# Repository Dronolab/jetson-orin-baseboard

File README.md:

# Dronolab Jetson Orin Carrier Board

Modified Version of [Jetson Orin Baseboard](https://github.com/antmicro/jetson-orin-baseboard) by [Antmicro](https://www.antmicro.com)

## Overview

This project contains hardware design files for a carrier board supporting NVIDIA Jetson Orin Nano and Jetson Orin NX System on Modules (SoMs). The board break-routes the typical IO interfaces from the SoM. Additionally, it exposes an expansion connector also known as the Payload Area Connector (PAC) that allows for an electrical connection for monitoring and control of any payload.

The design files were preapared in KiCad 7.x.

## Quick Start

Install Kicad's Latest Stable Release and Github Desktop. Clone this project using Github Desktop and make sure to set the option to contributing to the Dronolab Repository (not the Antmicro one). To make a change, create your own branch that describes the change being made. Once you are done, commit and push your changes. Finally, merge your branch to main and wait for approval.

## Key features

* DC Power connector
* MIPI CSI-2 interfaces
* USB-C 10 Gbps with DP Alternate Mode
* USB-C 10 Gbps + USB-C Uart
* M.2 key M for SSD
* 1Gb Ethernet
* Custom Payload Area Connector (PAC)
* RTC battery backup

## Project structure

The main directory contains KiCad PCB project files, a LICENSE, and a README.
The remaining files are stored in the following directories:

* `lib` - contains the component libraries
* `img` - contains graphics for this README
* `doc` - contains schematics in pdf form

## Licensing

This project is published under the [Apache-2.0](LICENSE) license.

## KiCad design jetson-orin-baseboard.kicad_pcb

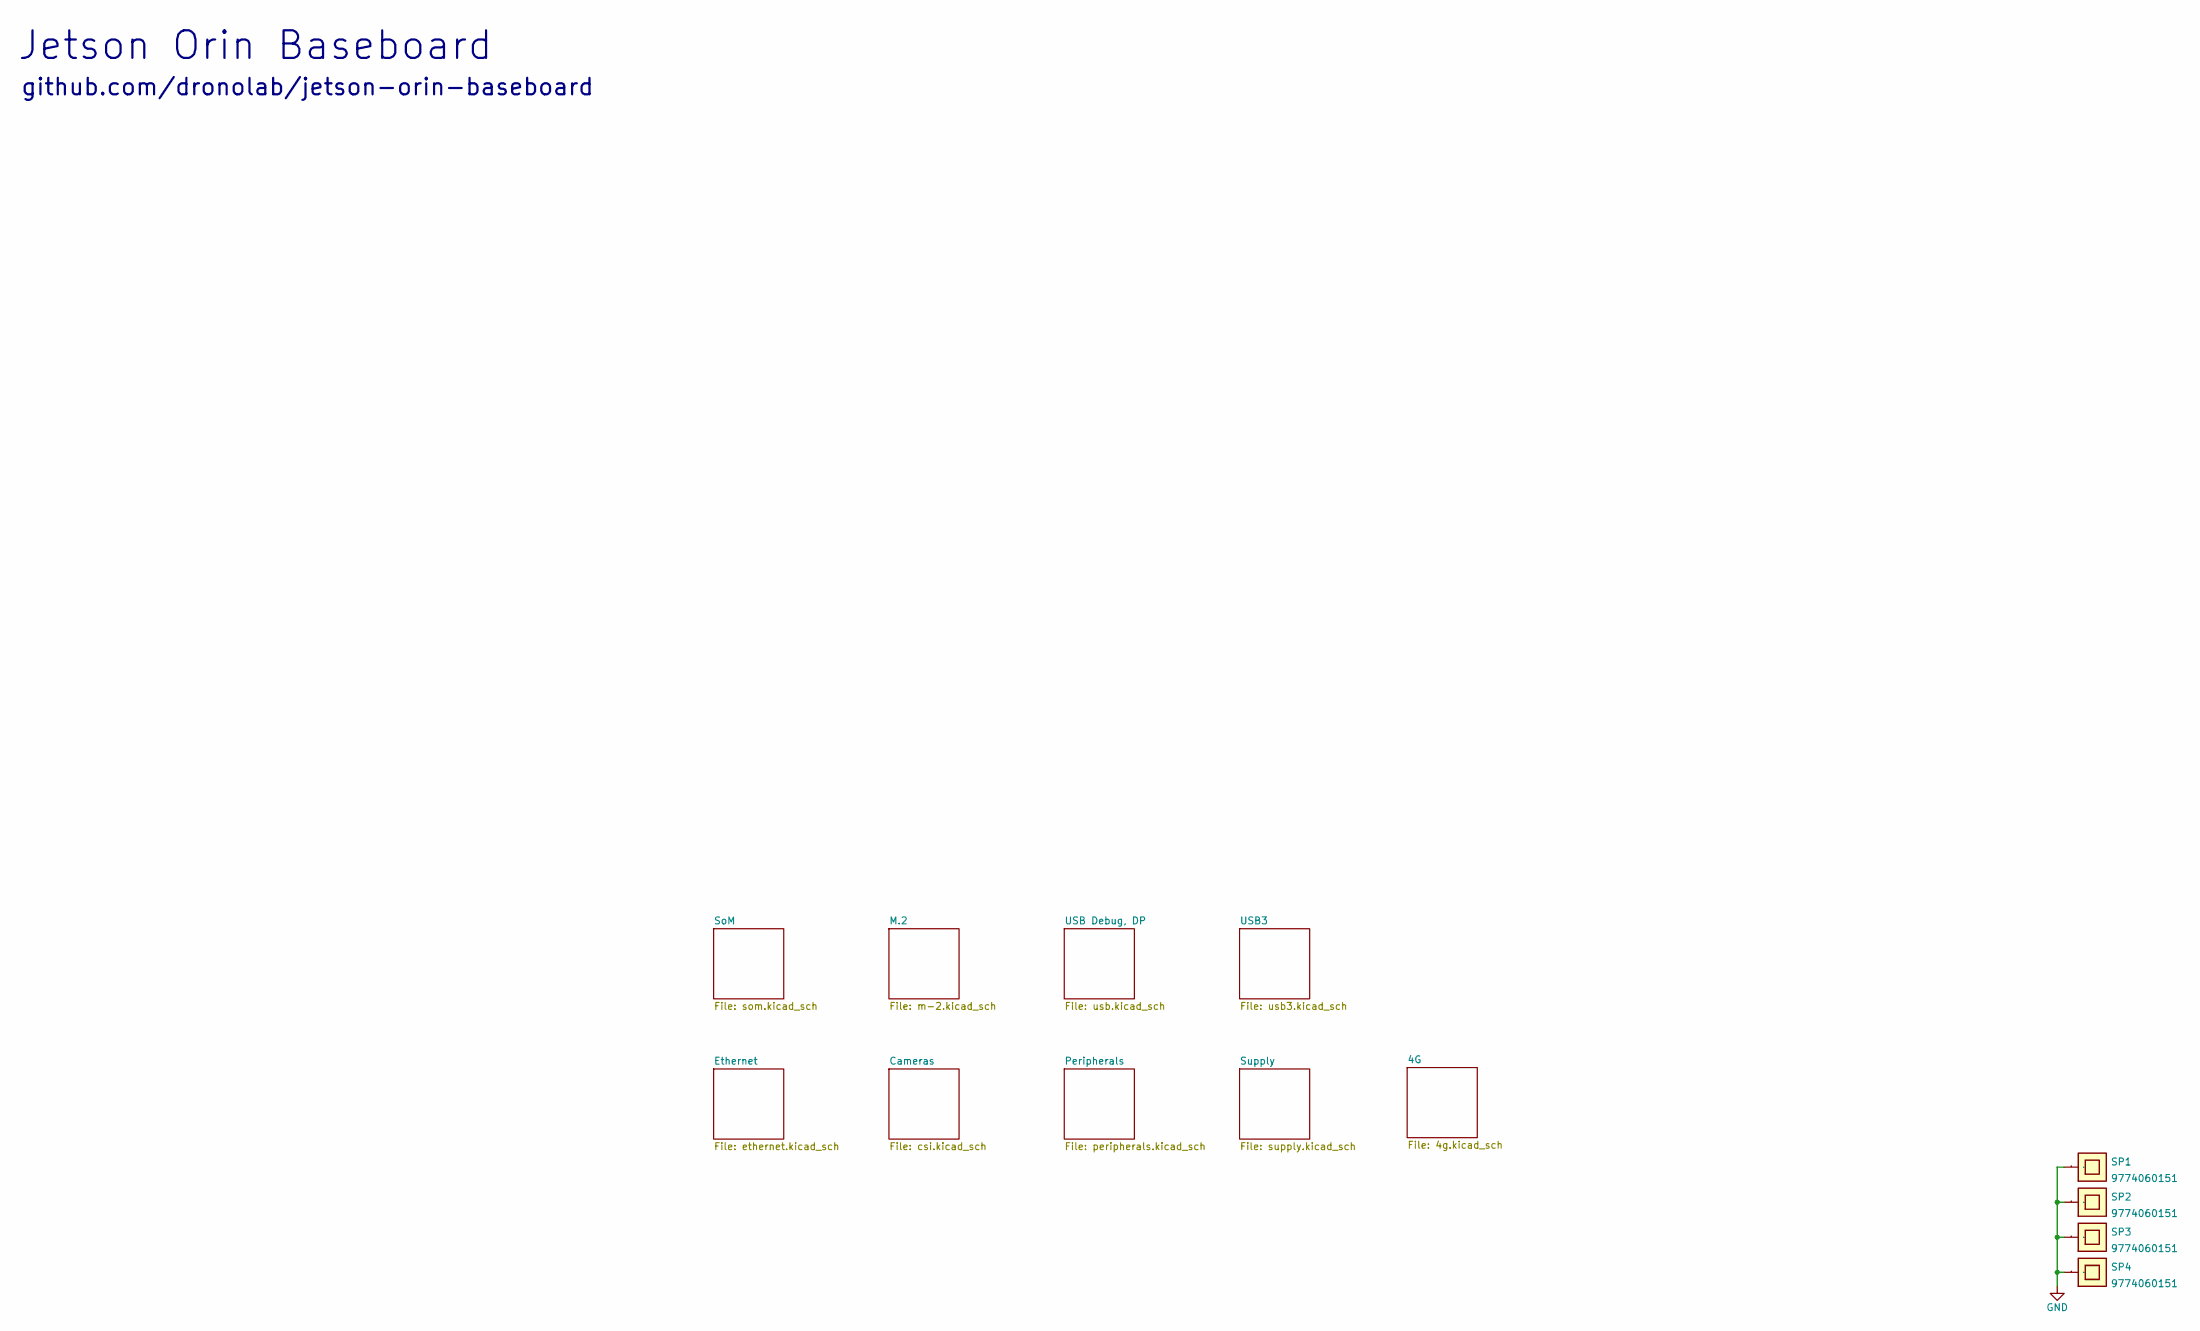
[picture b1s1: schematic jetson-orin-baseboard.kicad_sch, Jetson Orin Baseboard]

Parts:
SP1, SP2, SP3, SP4: 9774060151; MPN 9774060151

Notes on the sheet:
github.com/dronolab/jetson-orin-baseboard
Jetson Orin Baseboard

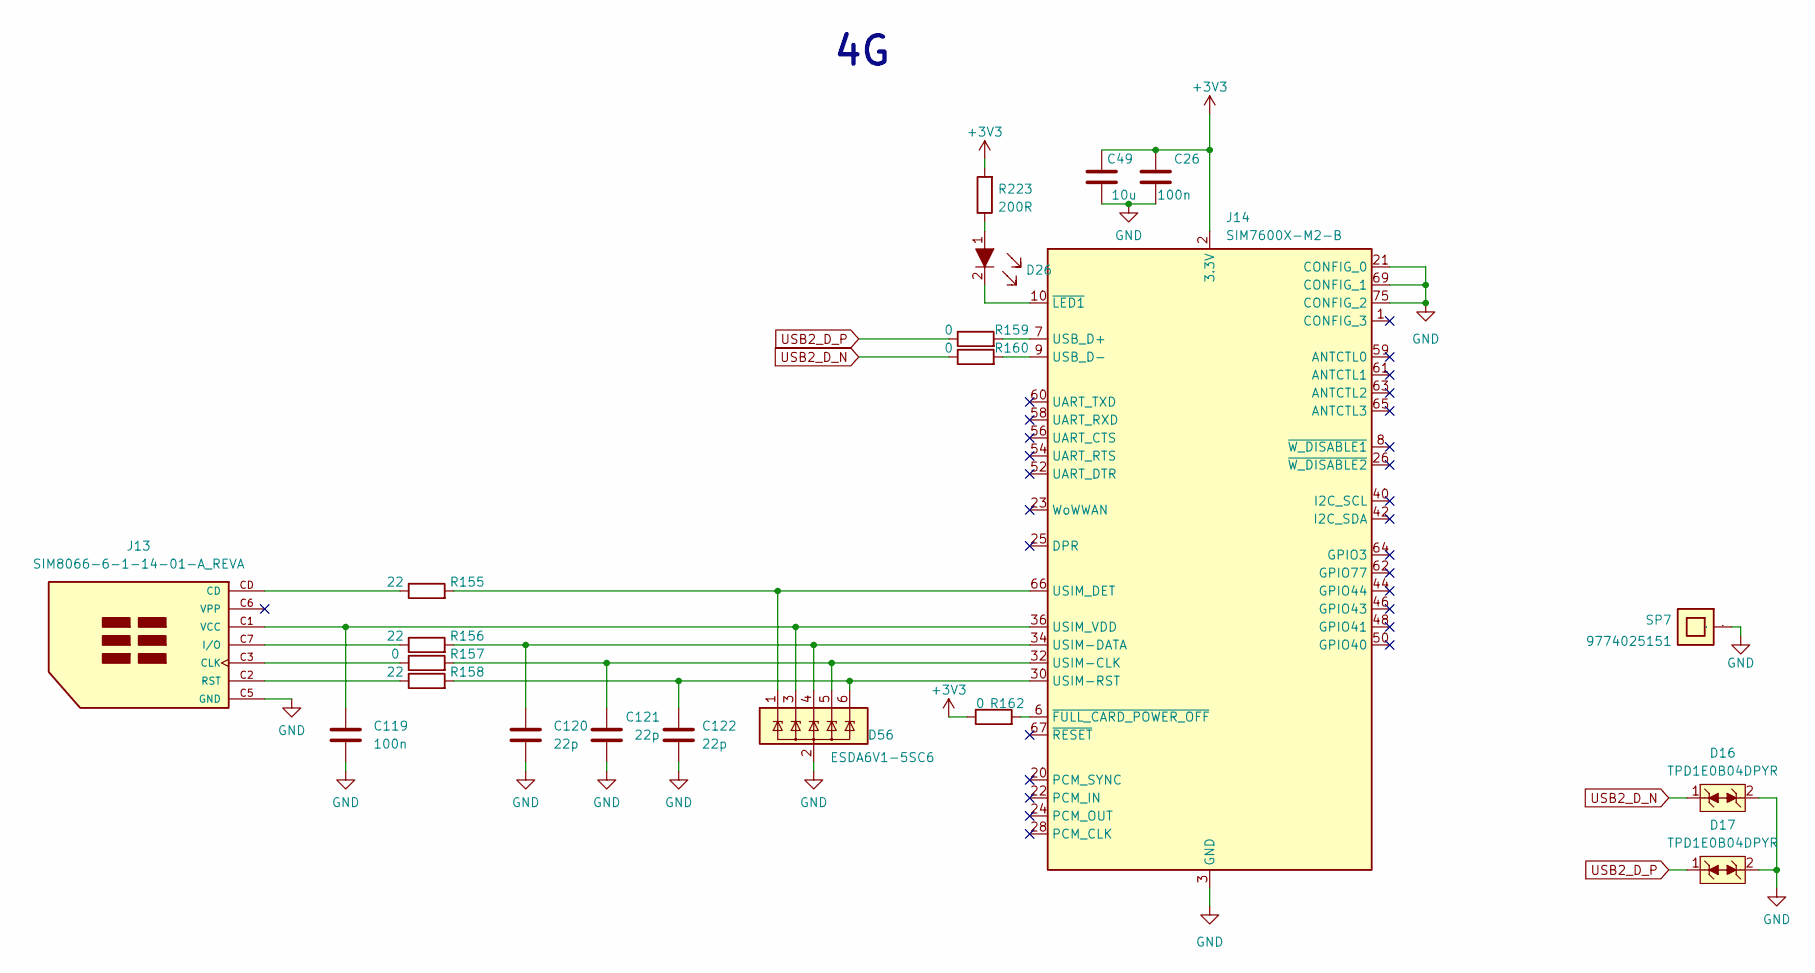
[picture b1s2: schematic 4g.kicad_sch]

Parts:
C26: C_100n_0402; 0402-cap; MPN GRM155R61H104KE14D
C49: C_10u_0402; 0402-cap; MPN CC0402MRX5R5BB106
C119: 100n; 0402-cap
C120, C121, C122: 22p; 0402-cap
D16, D17: TPD1E0B04DPYR; XDFN-2_1x0.60mm; MPN TPD1E0B04DPYR
D26: LTST-C190GKT; LED_0603; MPN LTST-C190GKT
D56: ESDA6V1-5SC6; SOT-23-6
J13: SIM8066-6-1-14-01-A_REVA; GCT_SIM8066-6-1-14-01-A_REVA; PARTREV REVA
J14: SIM7600X-M2-B; TE_2199230-3
R155, R156, R158: 22; 0402-res
R157, R159, R160, R162: 0; 0402-res
R223: R_200R_0402; 0402-res; MPN RC0402FR-07200RL
SP7: 9774025151; MPN 9774025151

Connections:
unnamed: D56.1 (IO1), J14.66 (USIM_DET), R155.2
unnamed: C119.1, D56.3 (IO2), J13.C1 (VCC), J14.36 (USIM_VDD)
unnamed: C120.1, D56.4 (IO3), J14.34 (USIM-DATA), R156.2
unnamed: C121.1, D56.5 (IO4), J14.32 (USIM-CLK), R157.2
unnamed: C122.1, D56.6 (IO5), J14.30 (USIM-RST), R158.2
unnamed: J13.C3 (CLK), R157.1
unnamed: J13.C7 (I/O), R156.1
unnamed: J13.CD, R155.1
unnamed: J13.C2 (RST), R158.1
unnamed: J14.7 (USB_D+), R159.2
unnamed: J14.9 (USB_D-), R160.2
unnamed: J14.6 (~FULL_CARD_POWER_OFF), R162.2
USB2_D_N: D16.1, R160.1; also elsewhere on the board
USB2_D_P: D17.1, R159.1; also elsewhere on the board

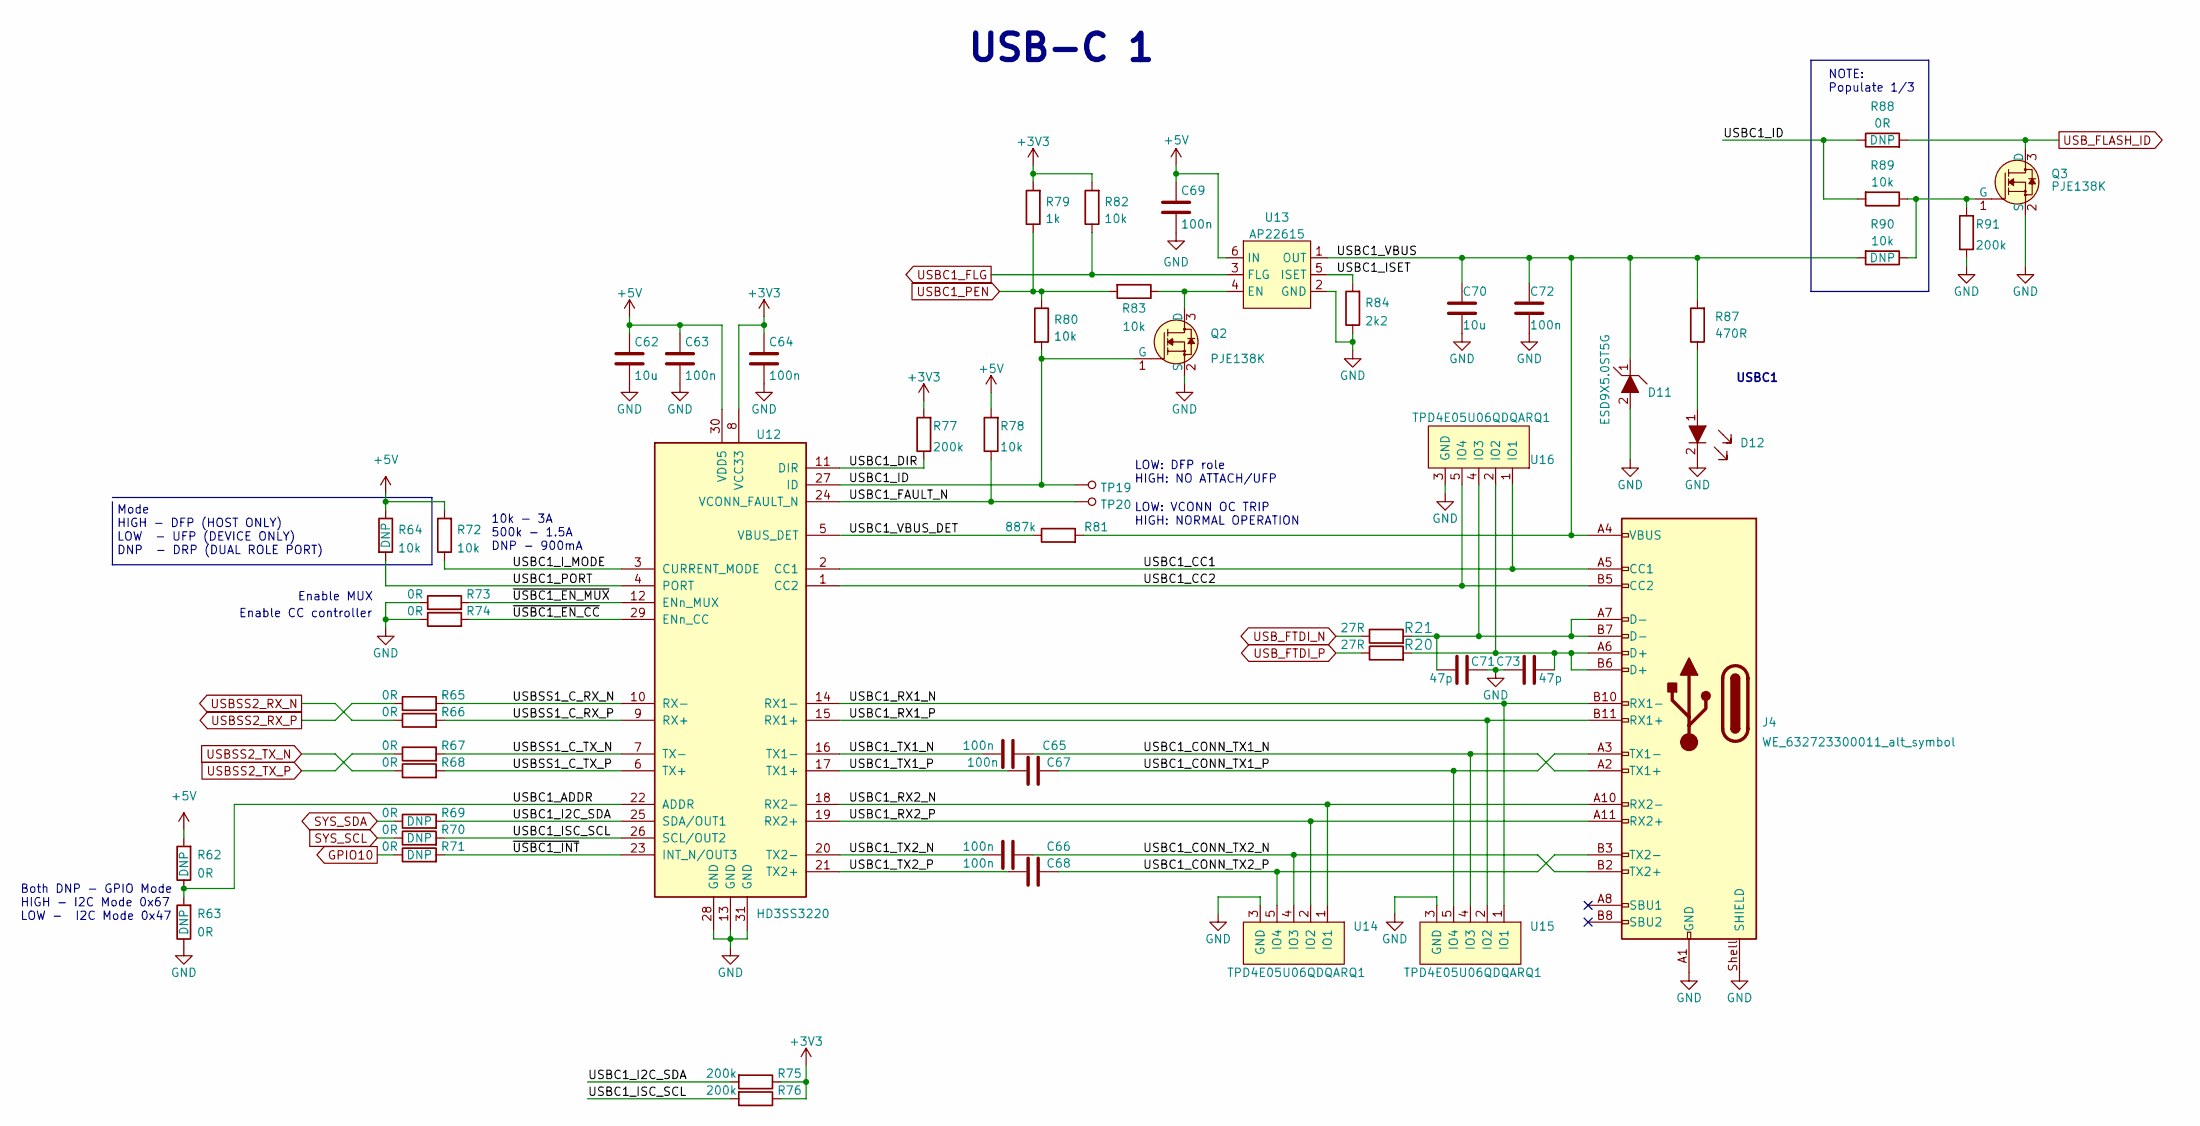
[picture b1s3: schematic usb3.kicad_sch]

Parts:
C62, C70: C_10u_0603; 0603-cap; MPN GRM188R61A106KE69D
C63, C64, C65, C66, C67, C68, C69, C72: C_100n_0402; 0402-cap; MPN GRM155R61H104KE14D
C71, C73: 47p; 0402-cap
D11: ESD9X5.0ST5G; SOD-923; MPN ESD9X5.0ST5G
D12: LTST-C190GKT; LED_0603; MPN LTST-C190GKT
J4: WE_632723300011_alt_symbol; WE_632723300011; MPN 632723300011
Q2, Q3: PJE138K; SOT-523; MPN PJE138K_R1_00001
R20, R21: R_27R_0402; 0402-res; MPN CRCW040227R0FKEDC
R62, R63, R65, R66, R67, R68, R69, R70, R71, R73, R74, R88: R_0R_0402; 0402-res; MPN ERJ2GE0R00X
R64, R72, R78, R80, R82, R83, R89, R90: R_10k_0402; 0402-res; MPN CRCW040210K0FKEDHP
R75, R76, R77, R91: R_200k_0402; 0402-res; MPN RC0402FR-07200KL
R79: R_1k_0402; 0402-res; MPN CR0402-FX-1001GLF
R81: R_887k_0402; 0402-res; MPN CR0402-FX-8873GLF
R84: R_2k2_0402; 0402-res; MPN RC0402FR-072K2L
R87: R_470R_0402; 0402-res; MPN CRCW0402470RFKED
TP19, TP20: TP_SMD_0_75MM; Testpoint_smd_0_75mm
U12: HD3SS3220; RNH0030A; MPN HD3SS3220RNHT
U13: AP22615; TSOT23-6; MPN AP22615AWU-7
U14, U15, U16: TPD4E05U06QDQARQ1; USON-10_2.5x1.0mm_P0.5mm; MPN TPD4E05U06QDQARQ1

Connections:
/USB3/USBC1_ADDR: R62.1, R63.2, U12.22 (ADDR)
/USB3/USBC1_CC1: J4.A5 (CC1), U12.2 (CC1), U16.1 (IO1), U16.10 (IO1)
/USB3/USBC1_CC2: J4.B5 (CC2), U12.1 (CC2), U16.5 (IO4), U16.6 (IO4)
/USB3/USBC1_CONN_TX1_N: C65.2, J4.A2 (TX1+), U15.4 (IO3), U15.7 (IO3)
/USB3/USBC1_CONN_TX1_P: C67.2, J4.A3 (TX1-), U15.5 (IO4), U15.6 (IO4)
/USB3/USBC1_CONN_TX2_N: C66.2, J4.B2 (TX2+), U14.4 (IO3), U14.7 (IO3)
/USB3/USBC1_CONN_TX2_P: C68.2, J4.B3 (TX2-), U14.5 (IO4), U14.6 (IO4)
/USB3/USBC1_DIR: R77.1, U12.11 (DIR)
/USB3/USBC1_FAULT_N: R78.1, TP20.1, U12.24 (VCONN_FAULT_N)
/USB3/USBC1_I2C_SDA: R69.2, R75.2, U12.25 (SDA/OUT1)
/USB3/USBC1_ID: Q2.1 (G), R80.2, R88.1, R89.2, TP19.1, U12.27 (ID)
/USB3/USBC1_ISC_SCL: R70.2, R76.2, U12.26 (SCL/OUT2)
/USB3/USBC1_ISET: R84.2, U13.5 (ISET)
/USB3/USBC1_I_MODE: R72.1, U12.3 (CURRENT_MODE)
/USB3/USBC1_PORT: R64.2, U12.4 (PORT)
/USB3/USBC1_RX1_N: J4.B10 (RX1-), U12.14 (RX1-), U15.1 (IO1), U15.10 (IO1)
/USB3/USBC1_RX1_P: J4.B11 (RX1+), U12.15 (RX1+), U15.2 (IO2), U15.9 (IO2)
/USB3/USBC1_RX2_N: J4.A10 (RX2-), U12.18 (RX2-), U14.1 (IO1), U14.10 (IO1)
/USB3/USBC1_RX2_P: J4.A11 (RX2+), U12.19 (RX2+), U14.2 (IO2), U14.9 (IO2)
/USB3/USBC1_TX1_N: C65.1, U12.16 (TX1-)
/USB3/USBC1_TX1_P: C67.1, U12.17 (TX1+)
/USB3/USBC1_TX2_N: C66.1, U12.20 (TX2-)
/USB3/USBC1_TX2_P: C68.1, U12.21 (TX2+)
/USB3/USBC1_VBUS: C70.1, C72.1, D11.1, J4.A4 (VBUS), J4.A9 (VBUS), J4.B4 (VBUS), J4.B9 (VBUS), R81.2, R87.2, R90.2, U13.1 (OUT)
/USB3/USBC1_VBUS_DET: R81.1, U12.5 (VBUS_DET)
/USB3/USBSS1_C_RX_N: R65.2, U12.10 (RX-)
/USB3/USBSS1_C_RX_P: R66.2, U12.9 (RX+)
/USB3/USBSS1_C_TX_N: R67.2, U12.7 (TX-)
/USB3/USBSS1_C_TX_P: R68.2, U12.6 (TX+)
/USB3/~USBC1_EN_CC: R74.2, U12.29 (ENn_CC)
/USB3/~USBC1_EN_MUX: R73.2, U12.12 (ENn_MUX)
/USB3/~USBC1_INT: R71.2, U12.23 (INT_N/OUT3)
/USB Debug, DP/PDC_CTL1: R21.1; also elsewhere on the board
GPIO10: R71.1; also elsewhere on the board
unnamed: D12.1, R87.1
unnamed: Q2.3 (D), R83.1, U13.4 (EN)
unnamed: Q3.1 (G), R89.1, R90.1, R91.2
SYS_SCL: R70.1; also elsewhere on the board
SYS_SDA: R69.1; also elsewhere on the board
USBC1_FLG: R82.1, U13.3 (FLG); also elsewhere on the board
USBC1_PEN: R79.1, R80.1, R83.2; also elsewhere on the board
USBSS2_RX_N: R66.1; also elsewhere on the board
USBSS2_RX_P: R65.1; also elsewhere on the board
USBSS2_TX_N: R68.1; also elsewhere on the board
USBSS2_TX_P: R67.1; also elsewhere on the board
USB_FLASH_ID: Q3.3 (D), R88.2; also elsewhere on the board

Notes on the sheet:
Mode HIGH - DFP (HOST ONLY) LOW - UFP (DEVICE ONLY) DNP - DRP (DUAL ROLE PORT)
Enable MUX
Both DNP - GPIO Mode HIGH - I2C Mode 0x67 LOW - I2C Mode 0x47
USB-C 1
10k - 3A 500k - 1.5A DNP - 900mA
LOW: DFP role HIGH: NO ATTACH/UFP
NOTE: Populate 1/3
USBC1
LOW: VCONN OC TRIP HIGH: NORMAL OPERATION
Enable CC controller

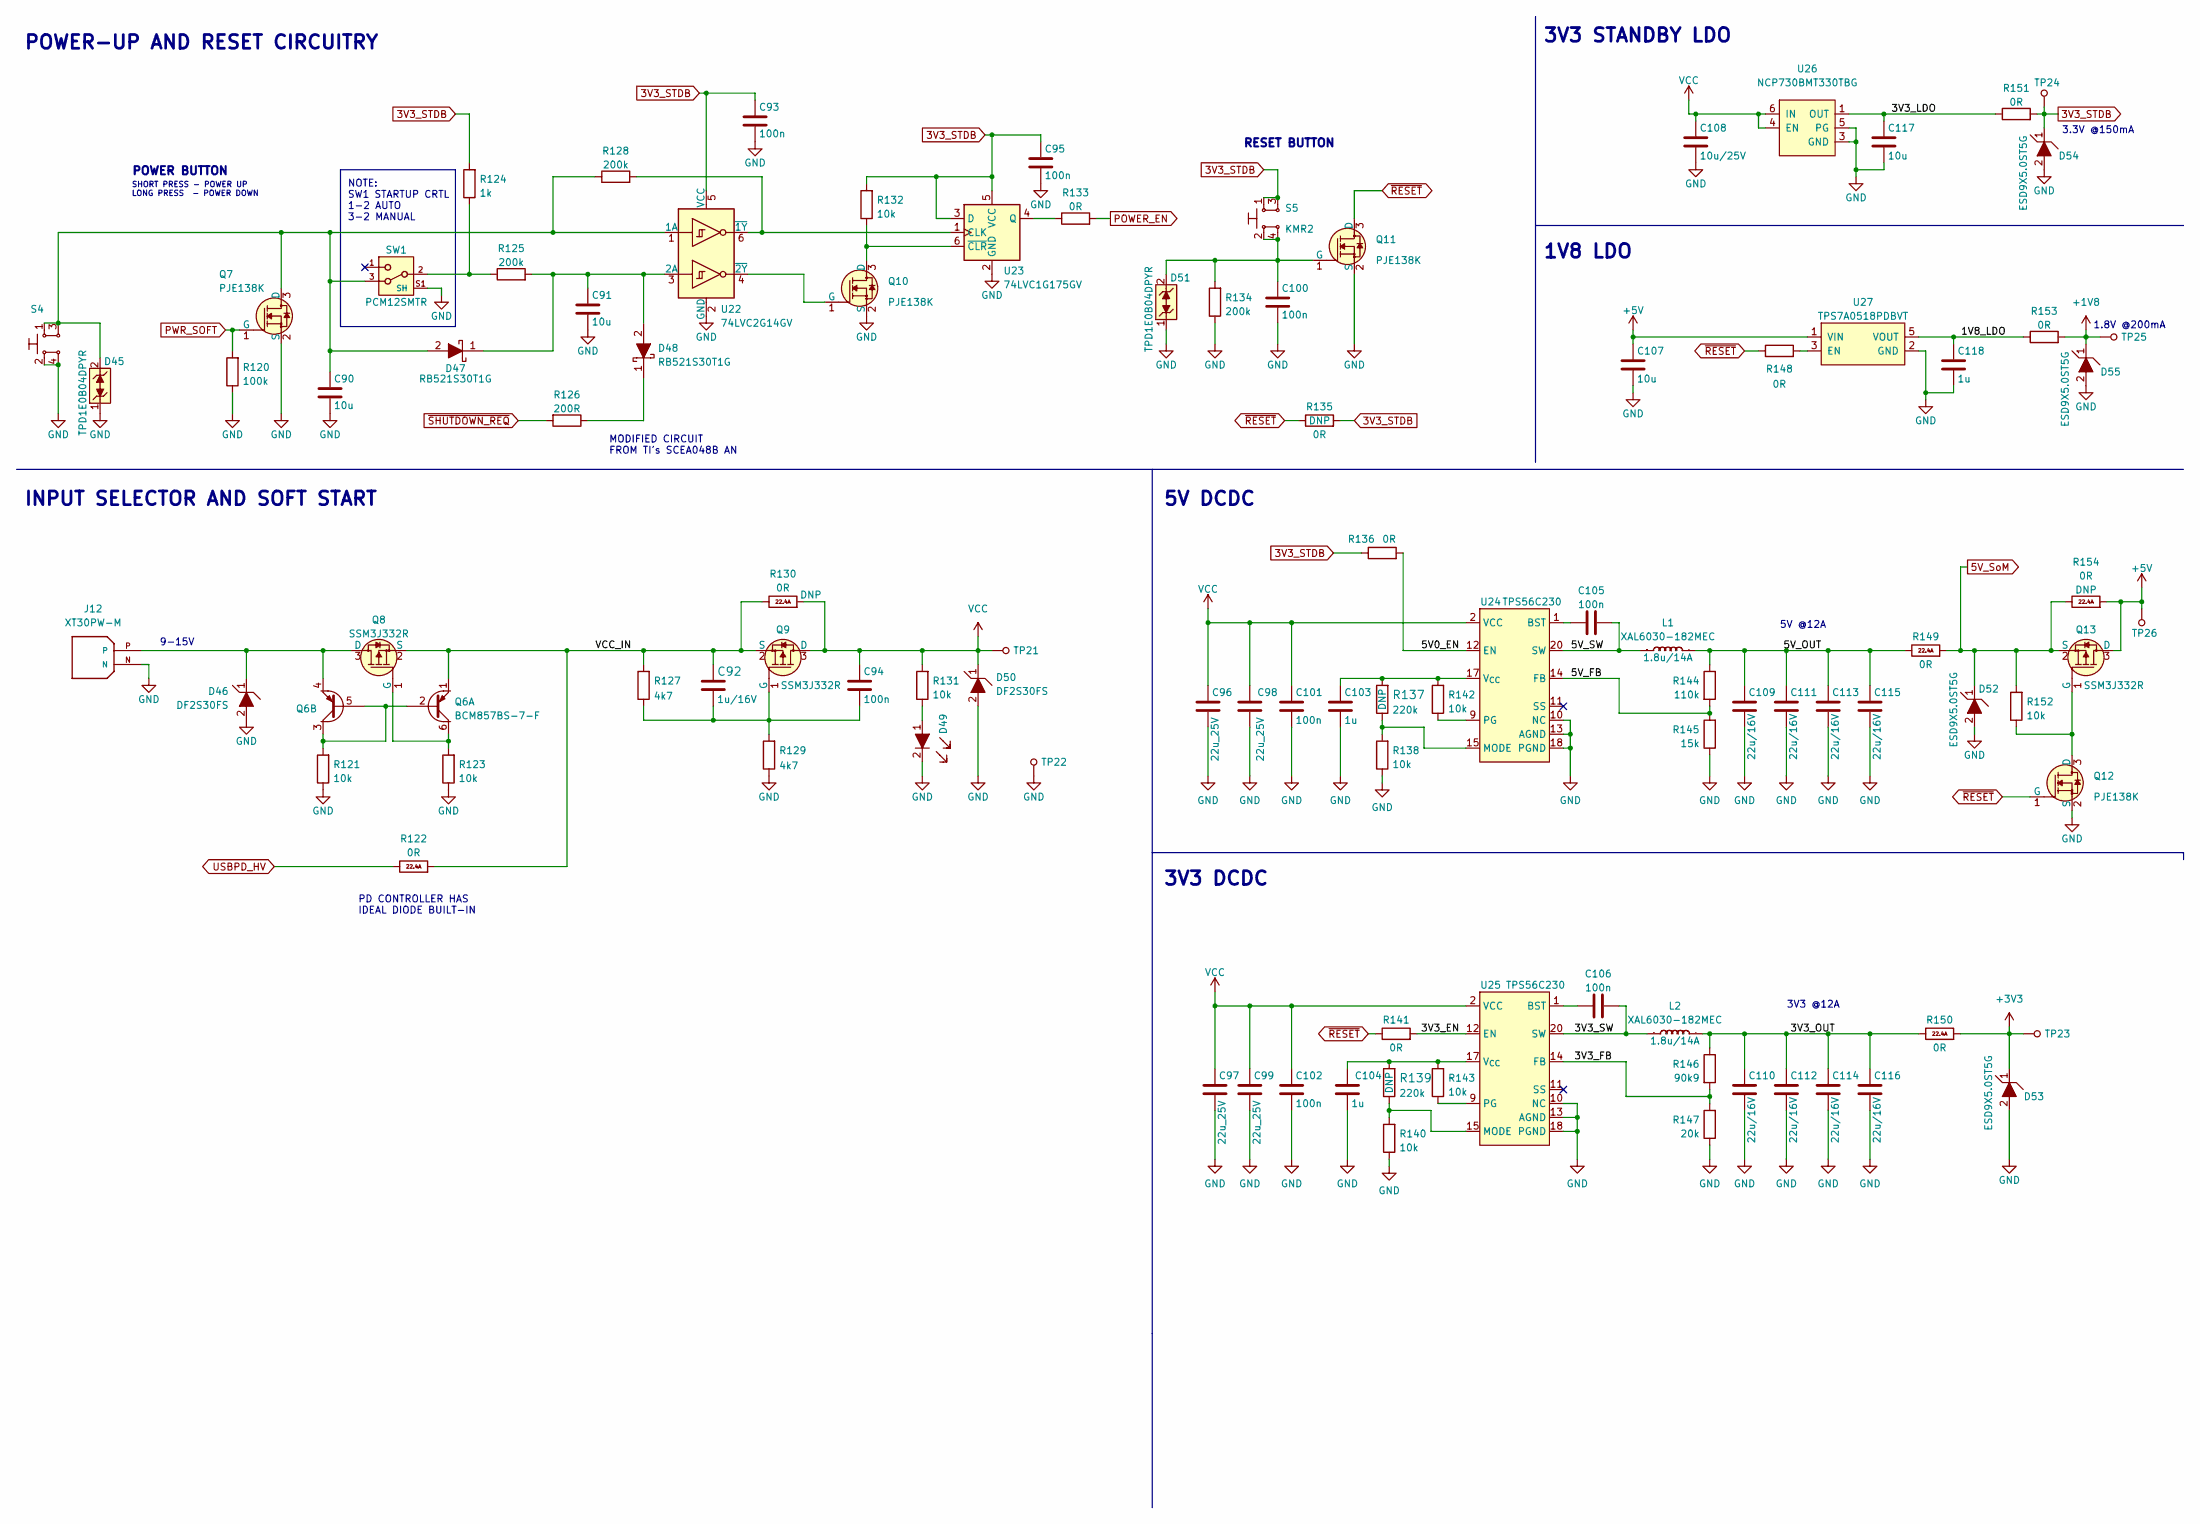
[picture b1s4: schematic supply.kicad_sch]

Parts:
C90, C91, C107, C117: C_10u_0402; 0402-cap; MPN CC0402MRX5R5BB106
C92: C_1u_0402_16V; 0402-cap; MPN C0402C105M4PACTU
C93, C94, C95, C100, C101, C102, C105, C106: C_100n_0402; 0402-cap; MPN GRM155R61H104KE14D
C96, C97, C98, C99: C_22u_0805_25V; 0805-cap; MPN CL21A226MAYNNNE
C103, C104, C118: C_1u_0402; 0402-cap; MPN C1005X6S1A105K050BC
C108: C_10u_25V_0603; 0603-cap; MPN C1608X5R1E106M080AC
C109, C110, C111, C112, C113, C114, C115, C116: C_22u_0603_16V; 0603-cap; MPN CL10A226MO7JZNC
D45, D51: TPD1E0B04DPYR; XDFN-2_1x0.60mm; MPN TPD1E0B04DPYR
D46, D50: DF2S30FS; SOD-923; MPN DF2S30FS
D47, D48: RB521S30T1G; SOD-523; MPN RB521S30T1G
D49: LTST-C190GKT; LED_0603; MPN LTST-C190GKT
D52, D53, D54, D55: ESD9X5.0ST5G; SOD-923; MPN ESD9X5.0ST5G
J12: XT30PW-M; AMASS_XT30PW-M; PARTREV 1.2
L1, L2: XAL6030-182MEC; Coilcraft-XAL6030; MPN XAL6030-182MEC
Q6: BCM857BS-7-F; SOT-363; MPN BCM857BS-7-F
Q7, Q10, Q11, Q12: PJE138K; SOT-523; MPN PJE138K_R1_00001
Q8, Q9, Q13: SSM3J332R; SOT-23-3; MPN SSM3J332R,LF
R120: R_100k_0402; 0402-res; MPN CRCW0402100KFKEDHP
R121, R123, R131, R132, R138, R140, R142, R143, R152: R_10k_0402; 0402-res; MPN CRCW040210K0FKEDHP
R122, R130, R149, R150, R154: R_0R_0603_HPWR; 0603-res; MPN PMR03EZPJ000
R124: R_1k_0402; 0402-res; MPN CR0402-FX-1001GLF
R125, R128, R134: R_200k_0402; 0402-res; MPN RC0402FR-07200KL
R126: R_200R_0402; 0402-res; MPN RC0402FR-07200RL
R127, R129: R_4k7_0402; 0402-res; MPN MCS04020C4701FE000
R133, R135, R136, R141, R148: R_0R_0402; 0402-res; MPN ERJ2GE0R00X
R137, R139: R_220k_0402; 0402-res; MPN ERJ-2RKF2203X
R144: R_110k_0402; 0402-res; MPN CR0402-FX-1103GLF
R145: R_15k_0402; 0402-res; MPN SFR01MZPF1502
R146: R_90k9_0402; 0402-res; MPN RC0402FR-0790K9L
R147: R_20k_0402; 0402-res; MPN CRCW040220K0FKED
R151, R153: R_0R_0603; 0603-res; MPN CR0603-J/-000ELF
S4, S5: KMR2; SW_SPST_4.2x2.8; MPN KMR211NGLFS
SW1: PCM12SMTR; MPN PCM13SMTR
TP21, TP22, TP23, TP24, TP25, TP26: TP_SMD_0_75MM; Testpoint_smd_0_75mm
U22: 74LVC2G14GV; SOT23-6L; MPN 74LVC2G14GV,125
U23: 74LVC1G175GV; SOT-23-6; MPN 74LVC1G175GV,125
U24, U25: TPS56C230; QFN-20_EP_3x3_Pitch0.45mm; MPN TPS56C230RJER
U26: NCP730BMT330TBG; WSON6_TI_2x2mm; MPN NCP730BMT330TBG
U27: TPS7A0518PDBVT; SOT-23-5; MPN TPS7A0518PDBVT

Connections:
3V3_STDB: C93.1, C95.1, D54.1, R124.2, R132.2, R135.2, R136.1, R151.2, S5.1, S5.3, TP24.1, U22.5 (VCC), U23.3 (D), U23.5 (VCC); also elsewhere on the board
5V_SoM: D52.1, Q13.2 (S), R149.2, R152.2, R154.1; also elsewhere on the board
+1V8: D55.1, R153.2, TP25.1; also elsewhere on the board
/Supply/1V8_LDO: C118.1, R153.1, U27.5 (VOUT)
/Supply/3V3_EN: R141.2, U25.12 (EN)
/Supply/3V3_FB: R146.2, R147.2, U25.14 (FB)
/Supply/3V3_LDO: C117.1, R151.1, U26.1 (OUT)
/Supply/3V3_OUT: C110.1, C112.1, C114.1, C116.1, L2.2, R146.1, R150.1
/Supply/3V3_SW: C106.2, L2.1, U25.6 (SW), U25.19 (SW), U25.20 (SW)
/Supply/5V0_EN: R136.2, U24.12 (EN)
/Supply/5V_FB: R144.2, R145.2, U24.14 (FB)
/Supply/5V_OUT: C109.1, C111.1, C113.1, C115.1, L1.2, R144.1, R149.1
/Supply/5V_SW: C105.2, L1.1, U24.6 (SW), U24.19 (SW), U24.20 (SW)
/Supply/VCC_IN: C92.1, Q6.1, Q8.2 (S), Q9.2 (S), R122.2, R127.2, R130.1
unnamed: D48.1, R126.1
unnamed: D49.1, R131.1
unnamed: Q6.2, Q6.3, Q6.5, R121.2
unnamed: C90.1, D45.2, D47.2, Q7.3 (D), R128.1, S4.1, S4.3, SW1.3, U22.1 (1A)
unnamed: D46.1, J12.P, Q6.4, Q8.3 (D)
unnamed: Q6.6, Q8.1 (G), R123.2
unnamed: C92.2, C94.2, Q9.1 (G), R127.1, R129.2
unnamed: Q10.3 (D), R132.1, U23.6 (~CLR)
unnamed: Q10.1 (G), U22.4 (~2Y)
unnamed: C100.1, D51.2, Q11.1 (G), R134.2, S5.2, S5.4
unnamed: Q12.3 (D), Q13.1 (G), R152.1
unnamed: R124.1, R125.1, SW1.2
unnamed: C91.1, D47.1, D48.2, R125.2, U22.3 (2A)
unnamed: R128.2, U22.6 (~1Y), U23.1 (CLK)
unnamed: R133.1, U23.4 (Q)
unnamed: C105.1, U24.1 (BST)
unnamed: R137.1, R138.2, U24.15 (MODE)
unnamed: R142.1, U24.9 (PG)
unnamed: C103.1, R137.2, R142.2, U24.17 (V_{CC})
unnamed: C106.1, U25.1 (BST)
unnamed: R139.1, R140.2, U25.15 (MODE)
unnamed: R143.1, U25.9 (PG)
unnamed: C104.1, R139.2, R143.2, U25.17 (V_{CC})
unnamed: R148.2, U27.3 (EN)
POWER_EN: R133.2; also elsewhere on the board
PWR_SOFT: Q7.1 (G), R120.2; also elsewhere on the board
USBPD_HV: R122.1; also elsewhere on the board
VCC: C94.1, C96.1, C97.1, C98.1, C99.1, C101.2, C102.2, C108.1, D50.1, Q9.3 (D), R130.2, R131.2, TP21.1, U24.2 (VCC), U24.3 (VCC), U24.4 (VCC), U24.5 (VCC), U25.2 (VCC), U25.3 (VCC), U25.4 (VCC), U25.5 (VCC), U26.4 (EN), U26.6 (IN)
~RESET: Q11.3 (D), Q12.1 (G), R135.1, R141.1, R148.1; also elsewhere on the board
~SHUTDOWN_REQ: R126.2; also elsewhere on the board

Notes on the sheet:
5V @12A
3V3 STANDBY LDO
3.3V @150mA
MODIFIED CIRCUIT FROM TI's SCEA048B AN
1V8 LDO
SHORT PRESS - POWER UP LONG PRESS - POWER DOWN
5V DCDC
NOTE: SW1 STARTUP CRTL 1-2 AUTO 3-2 MANUAL
POWER BUTTON
POWER-UP AND RESET CIRCUITRY
3V3 @12A
9-15V
3V3 DCDC
PD CONTROLLER HAS IDEAL DIODE BUILT-IN
INPUT SELECTOR AND SOFT START
1.8V @200mA
RESET BUTTON

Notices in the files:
parts and their libraries:
License: Apache-2.0
License: MIT
